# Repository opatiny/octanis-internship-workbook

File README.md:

# Internship at Octanis Instruments: workbook

Documentation resulting of my 20 weeks internship at Octanis Instruments.

To have global insight of what has been done during the internship:

- [Daily reports](./docs/general/dailyReports.md)
- [Conclusions of weekly meetings](./docs/general/weekly.md)

Various information that has been useful / doc written:

## Mechanics

- [Fusion 360 cheat sheet](./docs/mechanics/fusion360/fusion360CheatSheet.md)
- [3D printers doc](./docs/mechanics/3D-printing/printers.md)
  - [Slicers parameters of all prints](./docs/mechanics/3D-printing/printsParameters.md)
- [Laser cutting doc](./docs/mechanics/laser-cutting/laser-cutting.md)

## Electronics

- [Electronics theory](./docs/electronics/theory/theory.md)
- [KiCAD cheatsheet](./docs/electronics/pcb/kicad.md)
  - [Rigid-flex PCB](./docs/electronics/pcb/rigid-flex.md)

## Programming and IT

- [Setup a dual boot Windows / Xenial (Ubuntu)](./docs/programming/general/dualBoot.md)
- [Useful theory and definitions](./docs/programming/general/theory.md)
- [Programming environment setup procedure](./docs/programming/stm32Programming/environmentSetup.md)
- [CubeMX procedure](./docs/programming/stm32Programming/cubeMX.md)
- [C tips](./docs/stm32Programming/programming/stm32Programming/c.md)
- [FreeRTOS basic notions](./docs/programming/stm32Programming/freertos.md)
- [Firmware notes](./docs/programming/stm32Programming/firmware.md)
- [UAVCAN GUI Tools tips](./docs/programming/uavcan/uavcan.md)
- [Python tips](./docs/programming/python/python.md)

## Robotics

- [Robotics theory](./docs/robotics/theory.md)
- [ROS](./docs/robotics/ros.md)
- [Mobile Robotics course notes and exercices(own repo)](https://github.com/opatiny/mobile-robotics)
- [Robot Mapping course notes](./docs/robotics/robotMapping/robotMapping.md)

## Others

- [Windows tips](./docs/windows.md)
- [Useful webpages](./docs/links.md)

## VacRob

Main project that has been worked on: an autonomous vacuum cleaner robot that implements the technologies developed at Octanis Instuments.

Refer to the [**Vacuum cleaner robot project**](./vacrob/vacrob.md) MD file to access all the useful information.

## Small projects

Other small projects that have been worked on (aka small contributions):

- [Transistors logic gates](./smallProjects/logic_gates/logic_gates.md)
- [Micro-fluidics application](./smallProjects/microFluidics/microFluidics.md)
- [Making the photo-diodes board work](./smallProjects/photoDiodes/photoDiodes.md)
- [Bioreactor case](./smallProjects/bioreactor/bioreactor.md)

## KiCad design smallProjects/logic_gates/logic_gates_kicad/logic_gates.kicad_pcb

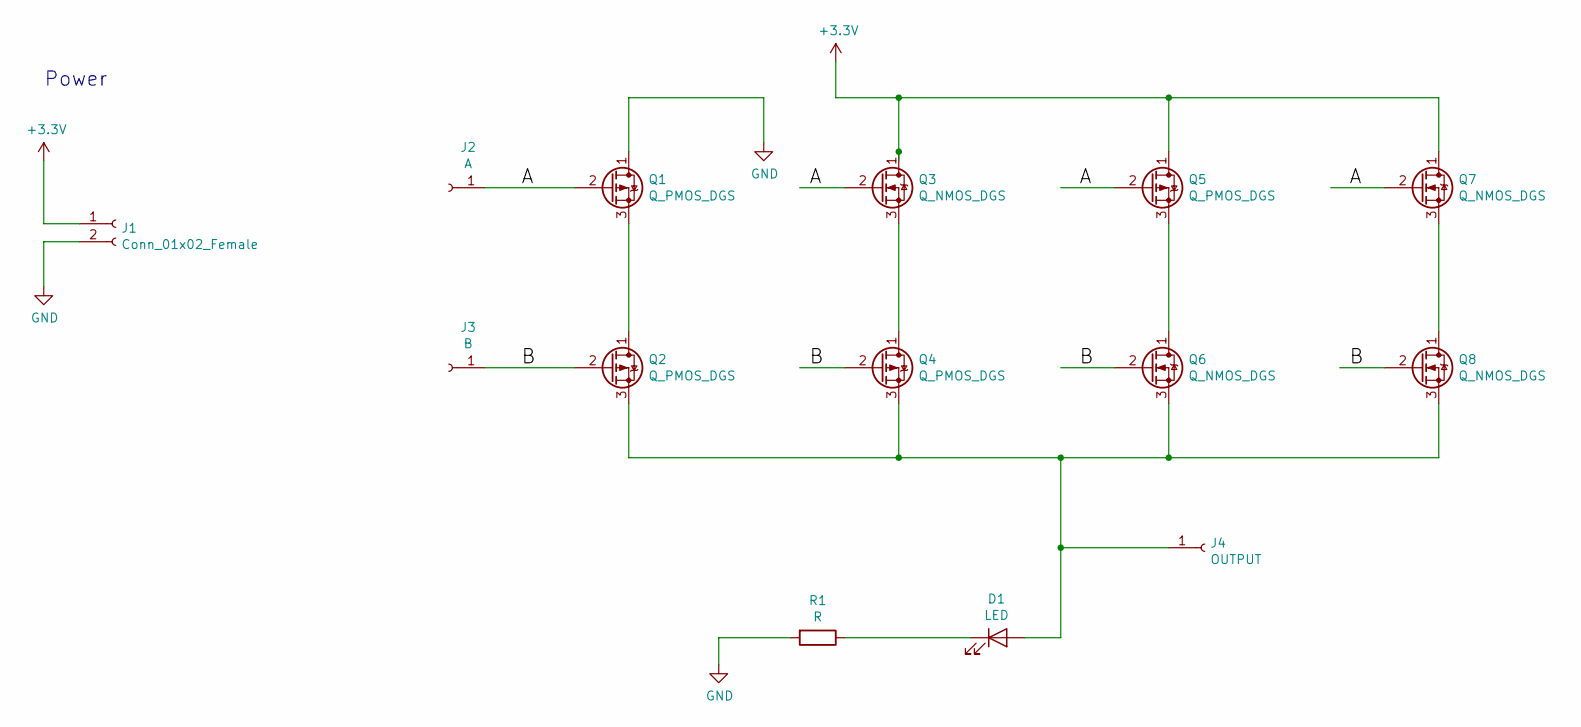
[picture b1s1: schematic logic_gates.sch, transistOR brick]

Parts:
D1: LED; LED_D5.0mm
J1: Conn_01x02_Female; SolderWirePad_1x02_P5.08mm_Drill1.5mm
J2: A; SolderWirePad_1x01_Drill1.5mm
J3: B; SolderWirePad_1x01_Drill1.5mm
J4: OUTPUT; SolderWirePad_1x01_Drill1.5mm
Q1, Q2, Q4, Q5: Q_PMOS_DGS; TSOT-23
Q3, Q6, Q7, Q8: Q_NMOS_DGS; TSOT-23
R1: R; R_1206_3216Metric

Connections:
+3V3: J1.1, Q3.1 (D), Q5.1 (D), Q7.1 (D)
/A: J2.1, Q1.2 (G), Q3.2 (G), Q5.2 (G), Q7.2 (G)
/B: J3.1, Q2.2 (G), Q4.2 (G), Q6.2 (G), Q8.2 (G)
GND: J1.2, Q1.1 (D), R1.2
unnamed: D1.1 (K), R1.1
unnamed: D1.2 (A), J4.1, Q2.3 (S), Q4.3 (S), Q6.3 (S), Q8.3 (S)
unnamed: Q1.3 (S), Q2.1 (D)
unnamed: Q3.3 (S), Q4.1 (D)
unnamed: Q5.3 (S), Q6.1 (D)
unnamed: Q7.3 (S), Q8.1 (D)

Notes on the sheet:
Power

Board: 2 copper layers, 14 parts (0 on the bottom side), 10 nets, no tracks yet.

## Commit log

2019-06-03 spelling mistake fix
2019-06-03 rename file
2019-06-03 work on roborock remake
2019-06-03 move datasheet and add pics
2019-06-04 worked in fusion and with prusa slicer/printers
2019-06-04 work in fusion on thread, corner and face parts
2019-06-05 working on fusion (small changes to corner and threadTest2)
2019-06-06 work on face, top and bottom models
2019-06-06 write doc about vacuum cleaner project
2019-06-07 doc from 05.06.2019
2019-06-11 doc of the day
2019-06-11 change capital letter and remove spaces of README
2019-06-11 write notes to self
2019-06-12 rename prusa 3D-printing and delete the apps folder level
2019-06-12 rearrange prusa exports into materials
2019-06-12 doc of the 2019.06.12
2019-06-12 removed apps folder (unnecessary level)
2019-06-13 add exports bracelet test
2019-06-13 work on hinge bent and clips
2019-06-13 started working on pcb design
2019-06-13 worked on docs
2019-06-13 continued project description
2019-06-14 export runes
2019-06-14 make simili TOC
2019-06-14 add h-bridge and proximity sensor datasheets
2019-06-14 working on pcb design
2019-06-14 various docs
2019-06-18 rename datasheets
2019-06-18 general doc from 2019.06.17
2019-06-18 started electronics paragraph of xiaomiRemake.md
2019-06-18 rename stl files with double extention
2019-06-18 fix git problem with double stl extention files
2019-06-18 work on electronics of vacuum robot: wheels teardown
2019-06-18 organise 3D docs
2019-06-18 general docs
2019-06-19 continue working on motor board and electronics
2019-06-19 daily doc
2019-06-20 follow kicad tutorials
2019-06-20 general doc
2019-06-21 continue understanding transistors and initiate sub-project
2019-06-21 started transistors building block mini-projects in tests folder
2019-06-21 continue learning kicad tricks
2019-06-24 rename folders and add connectors doc
2019-06-24 working on distance sensing and motor boards
2019-06-24 continue working on PCBs
2019-06-24 initiate photo-diodes and micro-fluidics small projects
2019-06-25 renamed docs/3D to docs/CAD
2019-06-25 started laser-cutting doc
2019-06-25 add valve datasheet
2019-06-27 working on mother distance pcb schematic and layout
2019-06-28 add navigation links to all md files
2019-06-28 working on mother and daughter distance boards
2019-06-28 global doc
2019-06-28 analysing what exists in microfluidics
2019-07-01 rename CAD to mechanics
2019-07-01 create robotics folder, work on electronics
2019-07-01 add schemes to logic gates project and add links to small projects
2019-07-02 create programming folder and work on robotics
2019-07-02 photo diodes: start code
2019-07-03 photo diodes: try generating 10MHz frequency
2019-07-03 electronics: learn about N and P type semiconductors
2019-07-03 robotics theory: start week 1 of mobile robotics
2019-07-03 programming: restructure folder
2019-07-10 tried repairing 3D printers
2019-07-10 photodiodes: tried generate 10Mhz
2019-07-10 xiaomi remake: add pictures
2019-07-10 xiaomi remake: soldered 3 distance module mother boards
2019-07-15 export top, side and bottom to dxf
2019-07-15 continue working on xiaomi remake
2019-07-15 update prints parameters and work on 3D printing
2019-07-15 export dxf and svg files for laser cutter (cutting out the case)
2019-07-15 new stuff about 3D printers
2019-07-16 add laser cutter information
2019-07-16 more files exported from fusion to 3D print and laser cut
2019-07-16 work on laser cutting
2019-07-16 general doc to xiaomi remake
2019-07-16 create gitignore
2019-07-16 mobile robotics, worked on course w2 and w3
2019-07-16 3D printer, robotics and general doc
2019-07-17 3D printing and Fusion tricks
2019-07-17 weekly meeting
2019-07-17 microfluidics: investigate valves
2019-07-17 minor change to xiaomiRemake.md
2019-07-17 working on microfluidics
2019-07-19 started case assembly
2019-07-19 add svg files of microfluidics mixers
2019-07-19 finished mobile robotics w3 theory
2019-07-22 had weekly meeting with Sam
2019-07-22 update daily reports
2019-07-23 add dual boot procedure
2019-07-23 watched w4 of MR
2019-07-23 started looking at content of Robot Mapping course
2019-07-23 ROS installation on Xenial
2019-07-23 finish MR w1 sheet0
2019-07-24 work on Mobile Robotics w1
2019-07-25 minor changes
2019-07-25 export stl file for small PCB case from fusion
2019-07-25 3D print smal PCB cases
2019-07-25 setup programming environment for STM32 on Ubuntu
2019-07-26 export small PCB case v8
2019-07-26 small PCB case v10
2019-07-26 write doc to programming environment for STM on Ubuntu
2019-07-26 rename programming vocabulary.md
2019-07-26 learning about FreeRTOS
2019-07-29 started programming distance module
2019-07-29 programming distance module
2019-07-29 add documentation to CO2 extraction from seas small project
2019-07-30 worked on uavcan for the distance module
2019-07-31 update folder structure programming
2019-07-31 work on robot code and reorder files
2019-09-02 started working on bioreactor co2 gaz bottle interface
2019-09-02 model new front wheel part
2019-09-02 add file to make remarks on VACROB
2019-09-03 working on bioreactor gaz bottle thread
2019-09-03 working in fusion360
2019-09-06 general doc and layout
2019-09-06 working on bioreactor case lid
2019-09-06 working on bioreactor lid
2019-09-06 work on front wheel part of VACROB
2019-09-09 work on bioreactor case
2019-09-11 work on bioreactor case main and base
2019-09-20 work on mobile robotics course
2019-09-23 work on MR course w3 and w4
2019-09-24 move files in VACROB project
2019-09-24 work on CAD of vacrob
2019-09-24 daily doc and minor electronics doc
2019-09-24 minor addition to vacrob mechanics doc
2019-09-25 continue working on vacrob mechanics and sort exports to subfolders
2019-09-25 daily docs and custom cable doc
2019-09-25 add image of pump part for vacrob
2019-09-26 reorganise bioreactor exports
2019-09-26 write doc to bioreactor project
2019-09-26 work on vacrob wheels fix
2019-09-30 work on vacrob hardware for second assembly
2019-10-01 renamed xiaomiRemake to vacrob
2019-10-02 add doc on vacrob mechanics and electronics assembly
2019-10-02 work on MR course w5
2019-10-02 work on vacrob case design
2019-10-03 rearange vacrob fusion360 and prusaSlicer exports
2019-10-03 worked on C programming
2019-10-04 work on vacrob case (pump output, pump face)
2019-10-04 update stm32progrogramming doc
2019-10-04 remove files generated by jupyter notebook
2019-10-04 learn some C
2019-10-07 learning C
2019-10-08 working on linked lists in C
2019-10-09 mainly finished my linked lists C module
2019-10-09 work on MR w5
2019-10-10 move MR theory to own repository (GitHub)
2019-10-11 add temporary stl file
2019-10-14 work on distance modules firmware
2019-10-15 solve debug in vscode and work on distance sensor i2c driver
2019-10-16 work on distance module fw
2019-10-17 try to communicate with distance sensor
2019-10-18 work on distance module firmware
2019-10-18 work on distance module fw and manage to communicate with vl53l
2019-10-18 fw and electronics doc
2019-10-23 daily doc, working on distance sensor continuous ranging
2019-10-24 vacrob: add doc specific to each mechanic assembly
2019-10-24 vacrob: model 3D printed bumper part
2019-10-24 vacrob: model 3D printed bumper part (stl)
2019-10-24 vacrob: create assemblies folders in inkscape exports
2019-10-24 add files for vacrob assembly 3
2019-10-24 vacrob: update links and enhance doc
2019-10-24 README: update vacrob links
2019-10-25 write vacrob/mechanics/assembly3.md doc
2019-10-28 working on distance module firmware
2019-10-29 work on dist module fw -> implement tasks for distances
2019-10-30 work on distance module fw: globally working
2019-11-04 work a bit on vacrob lidar and screen
2019-11-05 work on MR course
2019-11-06 work on vacrob lidar and touch screen
2019-11-07 daily and weekly doc
2019-11-07 working on vacrob: VNC works, lidar does not work yet
2019-11-08 working on vacrob lidar
2019-11-11 work on mp3 module for vacrob
2019-11-11 work on vacrob crosstalk problem
2019-11-13 working on vacrob speaker and crosstalk
2019-11-13 add vacrob face crosstalk test v6
2019-11-13 minor change to uavcan doc
2019-11-13 vacrob: reorganise distance module doc + new doc about sensor test
2019-11-13 vacrbo: work on distance sensor test
2019-11-13 vacrob general doc and daily doc
2019-11-13 vacrob: work on crosstalk hardware
2019-11-14 vacrob: work on crosstalk
2019-11-14 vacrob: distance sensor crosstalk cone
2019-11-14 soldered dist module rev2 and daily doc
2019-11-15 vacrob: work on crosstalk fix
2019-11-15 vacrob: working on crosstalk problem
2019-11-18 vacrob: reorganize exports and work on crosstalk face and bottom
2019-11-18 soldering distance module rev2 (5x)
2019-11-18 vacrob: adding pictures
2019-11-19 vacrob: and and rearrange pictures
2019-11-19 vacrob: dxf files for assembly4
2019-11-19 vacrob: rviz autolaunch works!
2019-11-21 vacrob: various exports
2019-11-21 vacrob: mechanical assembly 4 doc
2019-11-21 daily and general doc
2019-11-21 vacrob: add pictures of assembly 4
2019-11-21 vacrob: dist module crosstalk move plots to folder
2019-11-21 vacrob crosstalk: doc and pictures
2019-11-21 vacrob: fusion renderings
2019-11-21 vacrob: dist module sensor test doc
2019-11-21 vacrob: assemblies doc
2019-11-21 created vacrob software and motorModule folders
2019-11-22 remove ecarteur gcode
2019-11-22 vacrob: finally started motor module fw
2019-11-26 work on vacrob fw
2019-12-06 completing documentation
2019-12-09 having merge problems
2019-12-09 vacrob: rearrange and enhance motor module doc
2019-12-09 vacrob: rearrange and enhance distance module doc
2019-12-09 general doc and vacrob electronics
2020-03-10 vacrob: enhancing/completing documentation
2020-06-11 doc: update readme
2020-06-11 fix: typo
2021-03-05 add final robot pictures
2021-03-05 fix typo
